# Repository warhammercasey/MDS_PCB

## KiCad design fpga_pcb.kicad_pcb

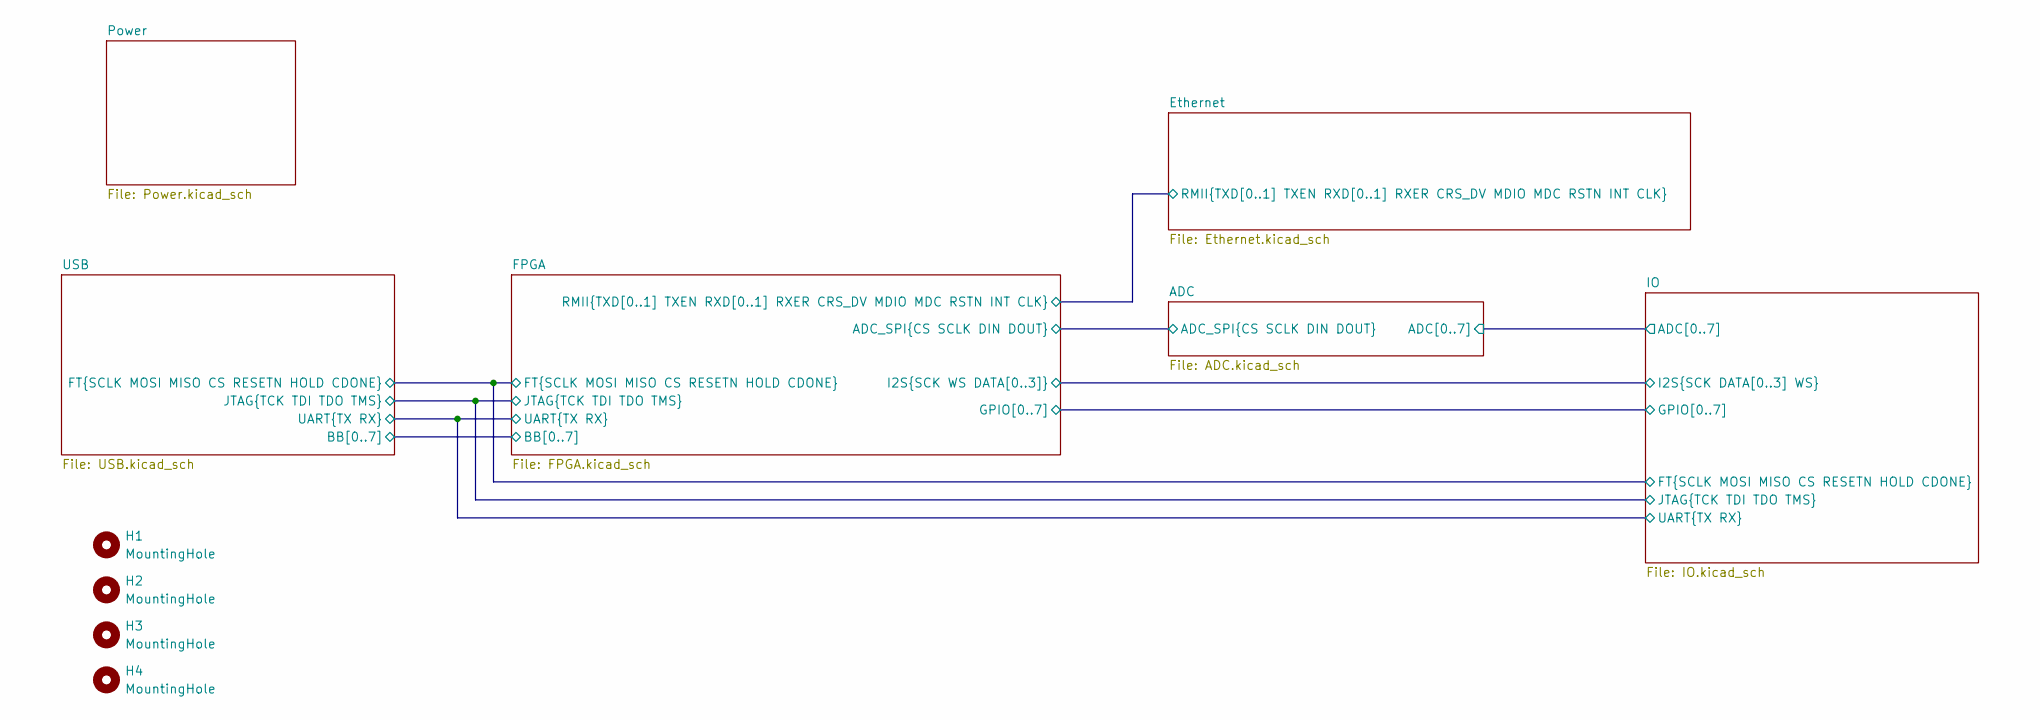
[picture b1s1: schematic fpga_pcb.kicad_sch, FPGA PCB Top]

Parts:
H1, H2, H3, H4: MountingHole; MountingHole_3.2mm_M3_DIN965_Pad

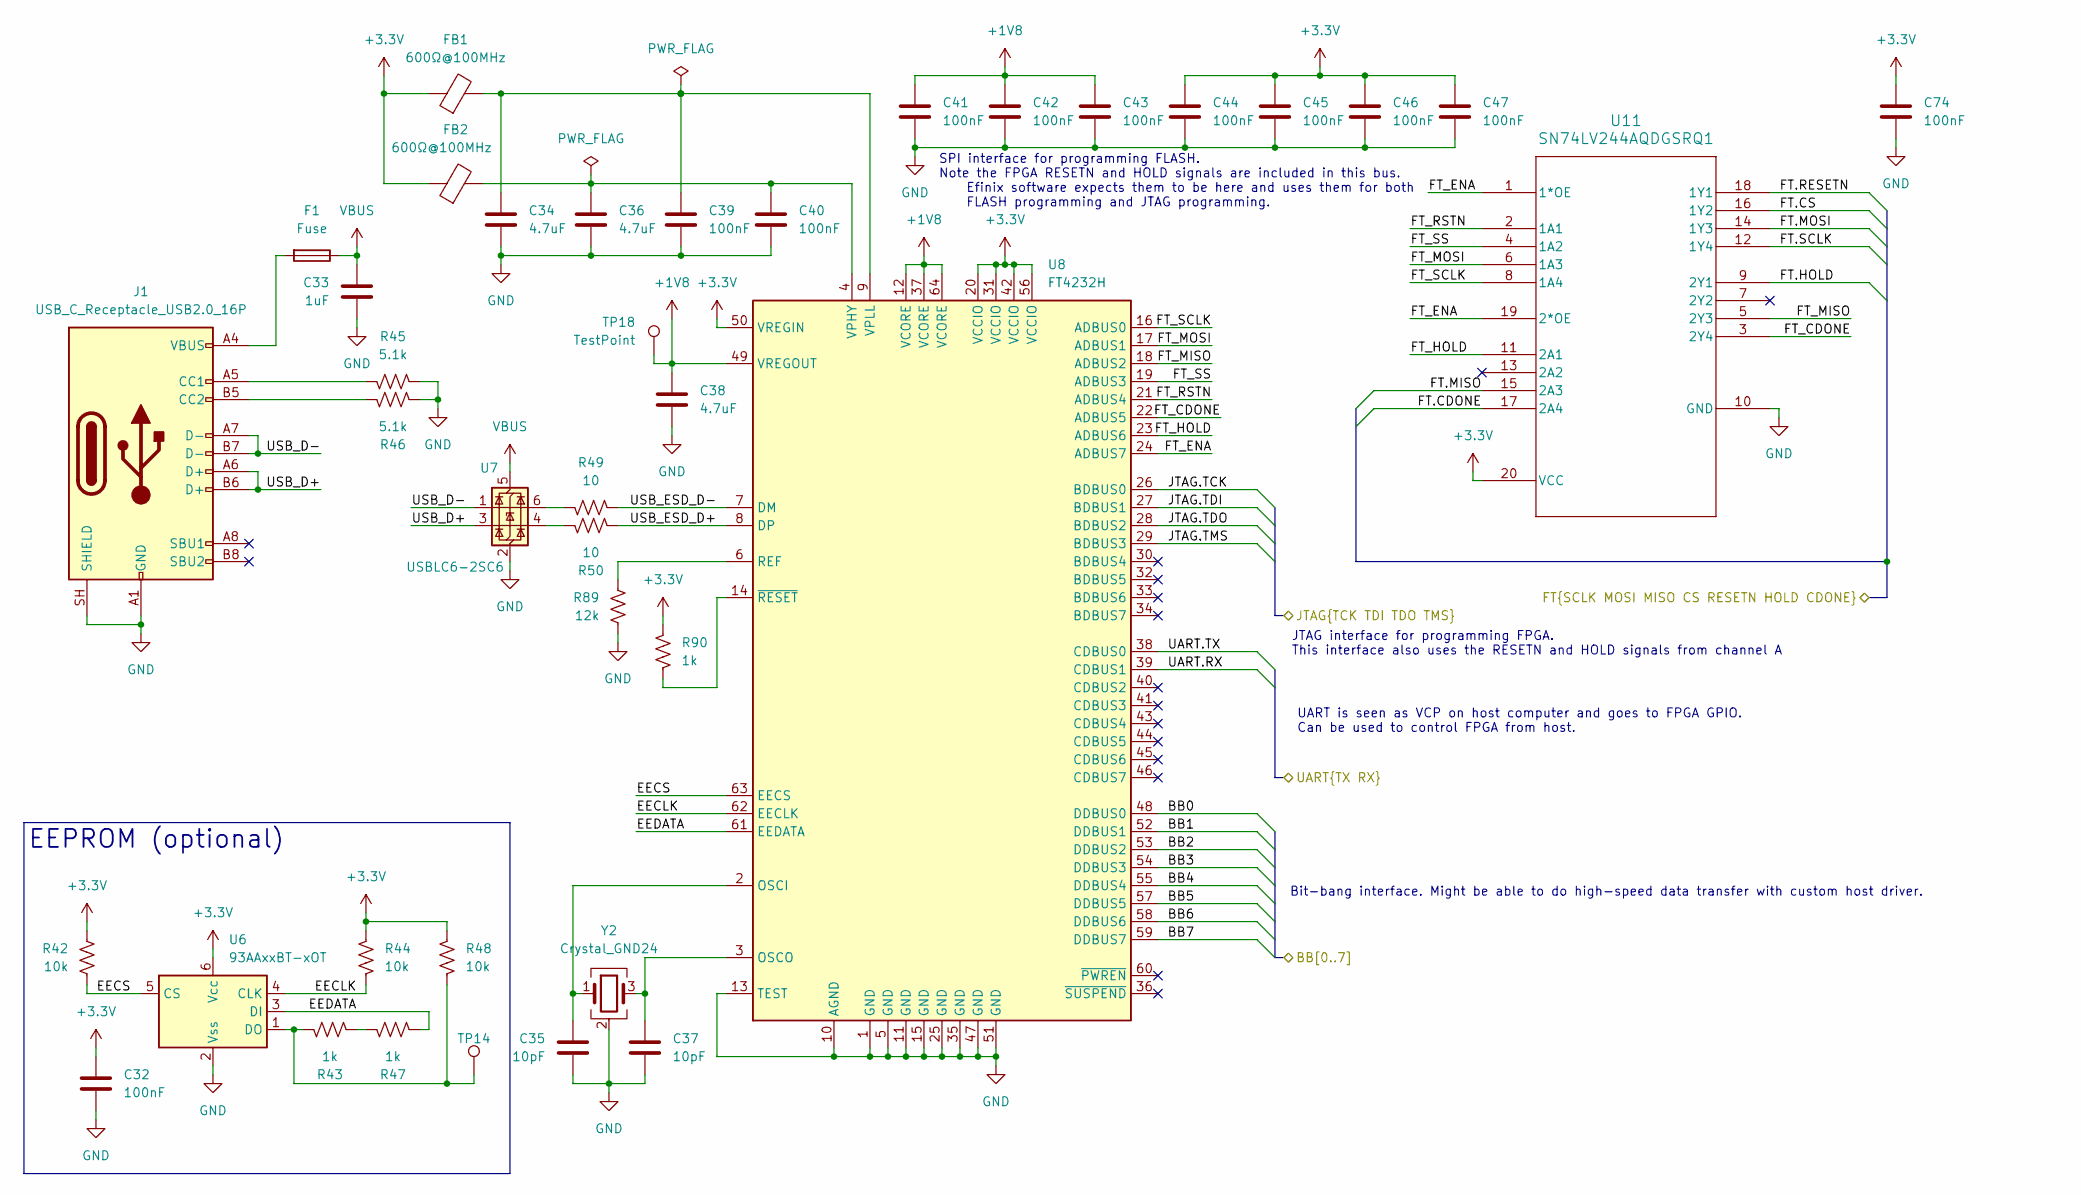
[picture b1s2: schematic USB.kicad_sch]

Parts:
C32, C39, C40, C41, C42, C43, C44, C45, C46, C47, C74: 100nF; C_0603_1608Metric; Digikey PN 1276-6854-1-ND
C33: 1uF; C_0603_1608Metric; Digikey PN 1276-1859-1-ND
C34, C36, C38: 4.7uF; C_0603_1608Metric; Digikey PN 1276-1045-1-ND
C35, C37: 10pF; C_0603_1608Metric; Digikey PN 1276-2149-1-ND
F1: Fuse; Fuse_0603_1608Metric; Digikey PN 5923-0686F7000-01CT-ND
FB1, FB2: 600Ω@100MHz; L_0603_1608Metric; Digikey PN 490-1014-1-ND
J1: USB_C_Receptacle_USB2.0_16P; USB_C_Receptacle_GCT_USB4105-xx-A_16P_TopMnt_Horizontal; Digikey PN 2073-USB4105-GF-ACT-ND
R42, R44, R48: 10k; R_0603_1608Metric; Digikey PN 311-10KLDCT-ND
R43, R47, R90: 1k; R_0603_1608Metric; Digikey PN 311-1.00KHRCT-ND
R45, R46: 5.1k; R_0603_1608Metric; Digikey PN 311-5.1KGRCT-ND
R49, R50: 10; R_0603_1608Metric; Digikey PN 311-10LDCT-ND
R89: 12k; R_0603_1608Metric; Digikey PN 311-12.0KHRCT-ND
TP14, TP18: TestPoint; TestPoint_Pad_D1.0mm
U6: 93AAxxBT-xOT; SOT-23-6; Digikey PN 93AA56BT-I/OTCT-ND
U7: USBLC6-2SC6; SOT-23-6; Mfr # USBLC6-2SC6; Digikey PN 497-5235-1-ND
U8: FT4232H; LQFP-64_10x10mm_P0.5mm
U11: SN74LV244AQDGSRQ1; VSSOP20_DGS_TEX; Digikey PN 296-SN74LV244AQDGSRQ1CT-ND
Y2: Crystal_GND24; Crystal_SMD_3225-4Pin_3.2x2.5mm; Digikey PN 2151-RH100-12.000-10-3030-TRCT-ND

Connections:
+1V8: C38.1, C41.1, C42.1, C43.1, TP18.1 (1_1), U8.12 (VCORE), U8.37 (VCORE), U8.49 (VREGOUT), U8.64 (VCORE)
+3.3V: C32.1, C44.1, C45.1, C46.1, C47.1, C74.1, FB1.1, FB2.1, R42.1, R44.1, R48.1, R90.1, U6.6 (Vcc), U8.20 (VCCIO), U8.31 (VCCIO), U8.42 (VCCIO), U8.50 (VREGIN), U8.56 (VCCIO), U11.20 (VCC); also elsewhere on the board
/FPGA/BB0: U8.48 (DDBUS0); also elsewhere on the board
/FPGA/BB1: U8.52 (DDBUS1); also elsewhere on the board
/FPGA/BB2: U8.53 (DDBUS2); also elsewhere on the board
/FPGA/BB3: U8.54 (DDBUS3); also elsewhere on the board
/FPGA/BB4: U8.55 (DDBUS4); also elsewhere on the board
/FPGA/BB5: U8.57 (DDBUS5); also elsewhere on the board
/FPGA/BB6: U8.58 (DDBUS6); also elsewhere on the board
/FPGA/BB7: U8.59 (DDBUS7); also elsewhere on the board
/FPGA/FT.CDONE: U11.17 (2A4); also elsewhere on the board
/FPGA/FT.CS: U11.16 (1Y2); also elsewhere on the board
/FPGA/FT.HOLD: U11.9 (2Y1); also elsewhere on the board
/FPGA/FT.MISO: U11.15 (2A3); also elsewhere on the board
/FPGA/FT.MOSI: U11.14 (1Y3); also elsewhere on the board
/FPGA/FT.RESETN: U11.18 (1Y1); also elsewhere on the board
/FPGA/FT.SCLK: U11.12 (1Y4); also elsewhere on the board
/FPGA/JTAG.TCK: U8.26 (BDBUS0); also elsewhere on the board
/FPGA/JTAG.TDI: U8.27 (BDBUS1); also elsewhere on the board
/FPGA/JTAG.TDO: U8.28 (BDBUS2); also elsewhere on the board
/FPGA/JTAG.TMS: U8.29 (BDBUS3); also elsewhere on the board
/FPGA/UART.RX: U8.39 (CDBUS1); also elsewhere on the board
/FPGA/UART.TX: U8.38 (CDBUS0); also elsewhere on the board
/USB/EECLK: R44.2, U6.4 (CLK), U8.62 (EECLK)
/USB/EECS: R42.2, U6.5 (CS), U8.63 (EECS)
/USB/EEDATA: R47.2, U6.3 (DI), U8.61 (EEDATA)
/USB/FT_CDONE: U8.22 (ADBUS5), U11.3 (2Y4)
/USB/FT_ENA: U8.24 (ADBUS7), U11.1 (1*OE), U11.19 (2*OE)
/USB/FT_HOLD: U8.23 (ADBUS6), U11.11 (2A1)
/USB/FT_MISO: U8.18 (ADBUS2), U11.5 (2Y3)
/USB/FT_MOSI: U8.17 (ADBUS1), U11.6 (1A3)
/USB/FT_RSTN: U8.21 (ADBUS4), U11.2 (1A1)
/USB/FT_SCLK: U8.16 (ADBUS0), U11.8 (1A4)
/USB/FT_SS: U8.19 (ADBUS3), U11.4 (1A2)
/USB/USB_D+: J1.A6 (D+), J1.B6 (D+), U7.3 (I/O2)
/USB/USB_D-: J1.A7 (D-), J1.B7 (D-), U7.1 (I/O1)
/USB/USB_ESD_D+: R50.1, U8.8 (DP)
/USB/USB_ESD_D-: R49.1, U8.7 (DM)
GND: C32.2, C33.2, C34.2, C35.2, C36.2, C37.2, C38.2, C39.2, C40.2, C41.2, C42.2, C43.2, C44.2, C45.2, C46.2, C47.2, C74.2, J1.A1 (GND), J1.A12 (GND), J1.B1 (GND), J1.B12 (GND), J1.SH (SHIELD), R45.1, R46.2, R89.2, U6.2 (Vss), U7.2 (GND), U8.1 (GND), U8.5 (GND), U8.10 (AGND), U8.11 (GND), U8.13 (TEST), U8.15 (GND), U8.25 (GND), U8.35 (GND), U8.47 (GND), U8.51 (GND), U11.10 (GND), Y2.2 (G), Y2.4 (G); also elsewhere on the board
unnamed: F1.2, J1.A4 (VBUS), J1.A9 (VBUS), J1.B4 (VBUS), J1.B9 (VBUS)
unnamed: J1.A5 (CC1), R45.2
unnamed: J1.B5 (CC2), R46.1
unnamed: R43.1, R47.1
unnamed: R49.2, U7.6 (I/O1)
unnamed: R50.2, U7.4 (I/O2)
unnamed: R43.2, R48.2, TP14.1 (1_1), U6.1 (DO)
unnamed: C35.1, U8.2 (OSCI), Y2.1
unnamed: C37.1, U8.3 (OSCO), Y2.3
unnamed: R89.1, U8.6 (REF)
unnamed: C36.1, C40.1, FB2.2, U8.4 (VPHY)
unnamed: C34.1, C39.1, FB1.2, U8.9 (VPLL)
unnamed: R90.2, U8.14 (~RESET)
VBUS: C33.1, F1.1, U7.5 (VBUS); also elsewhere on the board

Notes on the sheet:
EEPROM (optional)
SPI interface for programming FLASH. Note the FPGA RESETN and HOLD signals are included in this bus. Efinix software expects them to be here and uses them for both FLASH programming and JTAG programming.
UART is seen as VCP on host computer and goes to FPGA GPIO. Can be used to control FPGA from host.
JTAG interface for programming FPGA. This interface also uses the RESETN and HOLD signals from channel A
Bit-bang interface. Might be able to do high-speed data transfer with custom host driver.

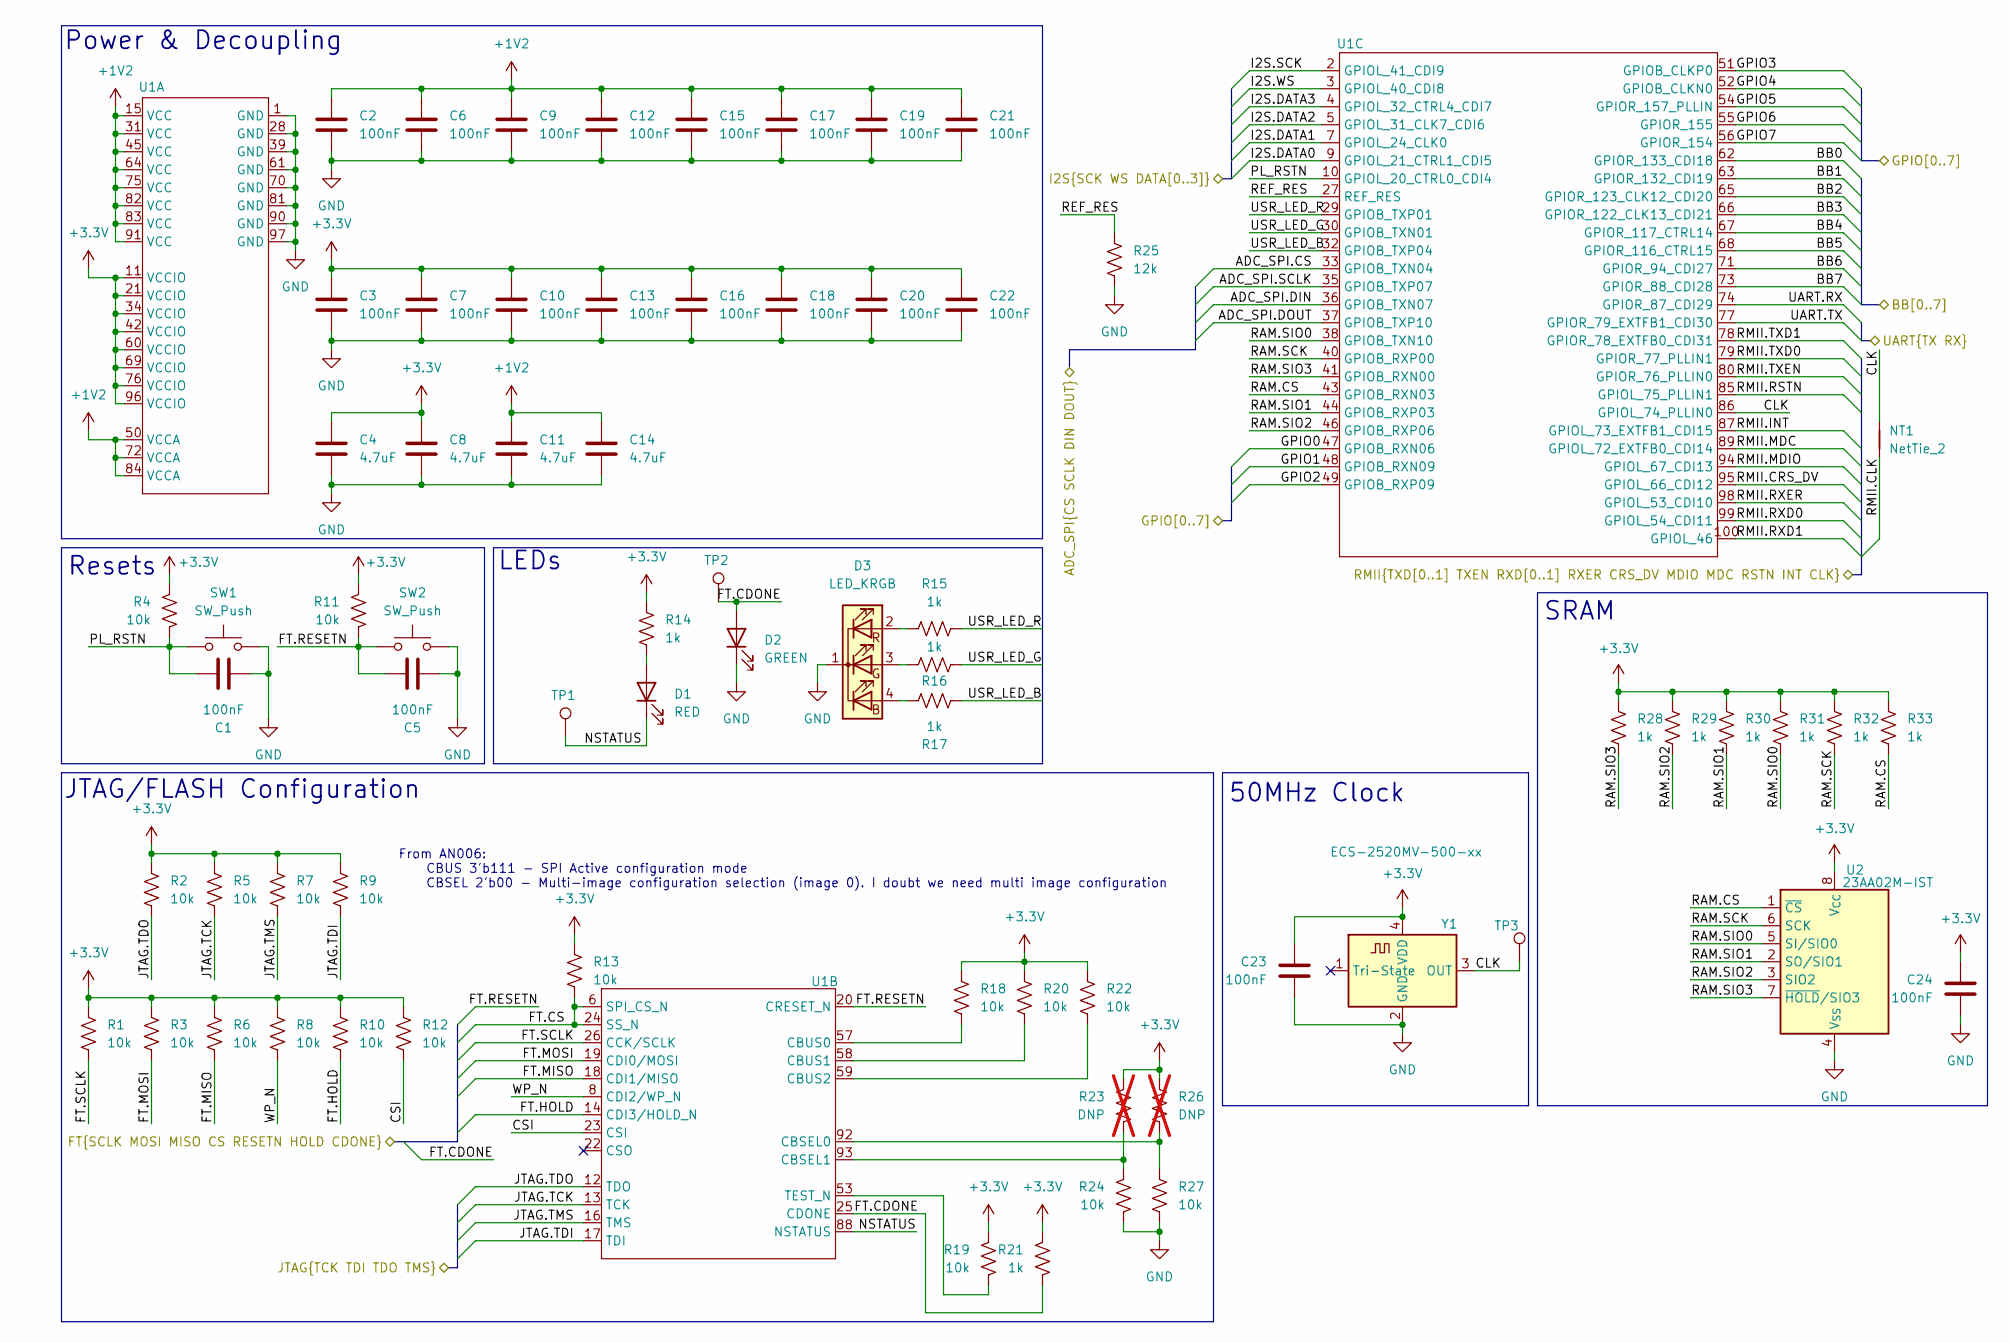
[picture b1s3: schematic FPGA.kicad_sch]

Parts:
C1, C2, C3, C5, C6, C7, C9, C10, C12, C13, C15, C16, C17, C18, C19, C20, C21, C22, C23, C24: 100nF; C_0603_1608Metric; Digikey PN 1276-6854-1-ND
C4, C8, C11, C14: 4.7uF; C_0603_1608Metric; Digikey PN 1276-1045-1-ND
D1: RED; LED_0603_1608Metric; Digikey PN 754-1123-1-ND
D2: GREEN; LED_0603_1608Metric; Digikey PN 754-1121-1-ND
D3: LED_KRGB; LED_LiteOn_LTST-C19HE1WT; Digikey PN 160-2162-1-ND
NT1: NetTie_2; NetTie-2_SMD_Pad0.5mm
R1, R2, R3, R4, R5, R6, R7, R8, R9, R10, R11, R12, R13, R18, R19, R20, R22, R24, R27: 10k; R_0603_1608Metric; Digikey PN 311-10KLDCT-ND
R14, R15, R16, R17, R21, R28, R29, R30, R31, R32, R33: 1k; R_0603_1608Metric; Digikey PN 311-1.00KHRCT-ND
R23, R26: DNP; R_0603_1608Metric; not fitted
R25: 12k; R_0603_1608Metric; Digikey PN 311-12.0KHRCT-ND
SW1, SW2: SW_Push; SW_Push_1P1T_NO_CK_KMR2; Digikey PN CKN10244CT-ND
TP1, TP2, TP3: TestPoint; TestPoint_Pad_D1.0mm
U1: LQFP-100_14x14mm_P0.5mm; DigiKey PN 2134-T20Q100F3C3-ND
U2: 23AA02M-IST; TSSOP-8_4.4x3mm_P0.65mm; Digikey PN 150-23AA02M-I/ST-ND
Y1: ECS-2520MV-500-xx; Oscillator_SMD_ECS_2520MV-xxx-xx-4Pin_2.5x2.0mm; Digikey PN XC2758CT-ND

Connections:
+1V2: C2.1, C6.1, C9.1, C11.1, C12.1, C14.1, C15.1, C17.1, C19.1, C21.1, U1.15 (VCC), U1.31 (VCC), U1.45 (VCC), U1.50 (VCCA), U1.64 (VCC), U1.72 (VCCA), U1.75 (VCC), U1.82 (VCC), U1.83 (VCC), U1.84 (VCCA), U1.91 (VCC); also elsewhere on the board
+3.3V: C3.1, C4.1, C7.1, C8.1, C10.1, C13.1, C16.1, C18.1, C20.1, C22.1, C23.1, C24.1, R1.1, R2.1, R3.1, R4.1, R5.1, R6.1, R7.1, R8.1, R9.1, R10.1, R11.1, R12.1, R13.1, R14.1, R18.1, R19.1, R20.1, R21.1, R22.1, R23.1, R26.1, R28.1, R29.1, R30.1, R31.1, R32.1, R33.1, U1.11 (VCCIO), U1.21 (VCCIO), U1.34 (VCCIO), U1.42 (VCCIO), U1.60 (VCCIO), U1.69 (VCCIO), U1.76 (VCCIO), U1.96 (VCCIO), U2.8 (V_{CC}), Y1.4 (VDD); also elsewhere on the board
/ADC/ADC_SPI.CS: U1.33 (GPIOB_TXN04); also elsewhere on the board
/ADC/ADC_SPI.DIN: U1.36 (GPIOB_TXN07); also elsewhere on the board
/ADC/ADC_SPI.DOUT: U1.37 (GPIOB_TXP10); also elsewhere on the board
/ADC/ADC_SPI.SCLK: U1.35 (GPIOB_TXP07); also elsewhere on the board
/Ethernet/RMII.CLK: NT1.1; also elsewhere on the board
/Ethernet/RMII.CRS_DV: U1.95 (GPIOL_66_CDI12); also elsewhere on the board
/Ethernet/RMII.INT: U1.87 (GPIOL_73_EXTFB1_CDI15); also elsewhere on the board
/Ethernet/RMII.MDC: U1.89 (GPIOL_72_EXTFB0_CDI14); also elsewhere on the board
/Ethernet/RMII.MDIO: U1.94 (GPIOL_67_CDI13); also elsewhere on the board
/Ethernet/RMII.RSTN: U1.85 (GPIOL_75_PLLIN1); also elsewhere on the board
/Ethernet/RMII.RXD0: U1.99 (GPIOL_54_CDI11); also elsewhere on the board
/Ethernet/RMII.RXD1: U1.100 (GPIOL_46); also elsewhere on the board
/Ethernet/RMII.RXER: U1.98 (GPIOL_53_CDI10); also elsewhere on the board
/Ethernet/RMII.TXD0: U1.79 (GPIOR_77_PLLIN1); also elsewhere on the board
/Ethernet/RMII.TXD1: U1.78 (GPIOR_78_EXTFB0_CDI31); also elsewhere on the board
/Ethernet/RMII.TXEN: U1.80 (GPIOR_76_PLLIN0); also elsewhere on the board
/FPGA/BB0: U1.62 (GPIOR_133_CDI18); also elsewhere on the board
/FPGA/BB1: U1.63 (GPIOR_132_CDI19); also elsewhere on the board
/FPGA/BB2: U1.65 (GPIOR_123_CLK12_CDI20); also elsewhere on the board
/FPGA/BB3: U1.66 (GPIOR_122_CLK13_CDI21); also elsewhere on the board
/FPGA/BB4: U1.67 (GPIOR_117_CTRL14); also elsewhere on the board
/FPGA/BB5: U1.68 (GPIOR_116_CTRL15); also elsewhere on the board
/FPGA/BB6: U1.71 (GPIOR_94_CDI27); also elsewhere on the board
/FPGA/BB7: U1.73 (GPIOR_88_CDI28); also elsewhere on the board
/FPGA/CLK: NT1.2, TP3.1 (1_1), U1.86 (GPIOL_74_PLLIN0), Y1.3 (OUT)
/FPGA/CSI: R12.2, U1.23 (CSI)
/FPGA/FT.CDONE: D2.2 (A), R21.2, TP2.1 (1_1), U1.25 (CDONE); also elsewhere on the board
/FPGA/FT.CS: R13.2, U1.6 (SPI_CS_N), U1.24 (SS_N); also elsewhere on the board
/FPGA/FT.HOLD: R10.2, U1.14 (CDI3/HOLD_N); also elsewhere on the board
/FPGA/FT.MISO: R6.2, U1.18 (CDI1/MISO); also elsewhere on the board
/FPGA/FT.MOSI: R3.2, U1.19 (CDI0/MOSI); also elsewhere on the board
/FPGA/FT.RESETN: C5.2, R11.2, SW2.1, U1.20 (CRESET_N); also elsewhere on the board
/FPGA/FT.SCLK: R1.2, U1.26 (CCK/SCLK); also elsewhere on the board
/FPGA/GPIO0: U1.47 (GPIOB_RXN06); also elsewhere on the board
/FPGA/GPIO1: U1.48 (GPIOB_RXN09); also elsewhere on the board
/FPGA/GPIO2: U1.49 (GPIOB_RXP09); also elsewhere on the board
/FPGA/GPIO3: U1.51 (GPIOB_CLKP0); also elsewhere on the board
/FPGA/GPIO4: U1.52 (GPIOB_CLKN0); also elsewhere on the board
/FPGA/GPIO5: U1.54 (GPIOR_157_PLLIN); also elsewhere on the board
/FPGA/GPIO6: U1.55 (GPIOR_155); also elsewhere on the board
/FPGA/GPIO7: U1.56 (GPIOR_154); also elsewhere on the board
/FPGA/I2S.DATA0: U1.9 (GPIOL_21_CTRL1_CDI5); also elsewhere on the board
/FPGA/I2S.DATA1: U1.7 (GPIOL_24_CLK0); also elsewhere on the board
/FPGA/I2S.DATA2: U1.5 (GPIOL_31_CLK7_CDI6); also elsewhere on the board
/FPGA/I2S.DATA3: U1.4 (GPIOL_32_CTRL4_CDI7); also elsewhere on the board
/FPGA/I2S.SCK: U1.2 (GPIOL_41_CDI9); also elsewhere on the board
/FPGA/I2S.WS: U1.3 (GPIOL_40_CDI8); also elsewhere on the board
/FPGA/JTAG.TCK: R5.2, U1.13 (TCK); also elsewhere on the board
/FPGA/JTAG.TDI: R9.2, U1.17 (TDI); also elsewhere on the board
/FPGA/JTAG.TDO: R2.2, U1.12 (TDO); also elsewhere on the board
/FPGA/JTAG.TMS: R7.2, U1.16 (TMS); also elsewhere on the board
/FPGA/NSTATUS: D1.1 (K), TP1.1 (1_1), U1.88 (NSTATUS)
/FPGA/PL_RSTN: C1.2, R4.2, SW1.1, U1.10 (GPIOL_20_CTRL0_CDI4)
/FPGA/RAM.CS: R33.2, U1.43 (GPIOB_RXN03), U2.1 (~CS)
/FPGA/RAM.SCK: R32.2, U1.40 (GPIOB_RXP00), U2.6 (SCK)
/FPGA/RAM.SIO0: R31.2, U1.38 (GPIOB_TXN10), U2.5 (SI/SIO0)
/FPGA/RAM.SIO1: R30.2, U1.44 (GPIOB_RXP03), U2.2 (SO/SIO1)
/FPGA/RAM.SIO2: R29.2, U1.46 (GPIOB_RXP06), U2.3 (SIO2)
/FPGA/RAM.SIO3: R28.2, U1.41 (GPIOB_RXN00), U2.7 (~HOLD/SIO3)
/FPGA/REF_RES: R25.1, U1.27 (REF_RES)
/FPGA/UART.RX: U1.74 (GPIOR_87_CDI29); also elsewhere on the board
/FPGA/UART.TX: U1.77 (GPIOR_79_EXTFB1_CDI30); also elsewhere on the board
/FPGA/USR_LED_B: R17.1, U1.32 (GPIOB_TXP04)
/FPGA/USR_LED_G: R16.2, U1.30 (GPIOB_TXN01)
/FPGA/USR_LED_R: R15.2, U1.29 (GPIOB_TXP01)
/FPGA/WP_N: R8.2, U1.8 (CDI2/WP_N)
GND: C1.1, C2.2, C3.2, C4.2, C5.1, C6.2, C7.2, C8.2, C9.2, C10.2, C11.2, C12.2, C13.2, C14.2, C15.2, C16.2, C17.2, C18.2, C19.2, C20.2, C21.2, C22.2, C23.2, C24.2, D2.1 (K), D3.1 (K), R24.2, R25.2, R27.2, SW1.2, SW2.2, U1.1 (GND), U1.28 (GND), U1.39 (GND), U1.61 (GND), U1.70 (GND), U1.81 (GND), U1.90 (GND), U1.97 (GND), U2.4 (V_{SS}), Y1.2 (GND); also elsewhere on the board
unnamed: D1.2 (A), R14.2
unnamed: D3.4 (BA), R17.2
unnamed: D3.3 (GA), R16.1
unnamed: D3.2 (RA), R15.1
unnamed: R26.2, R27.1, U1.92 (CBSEL0)
unnamed: R23.2, R24.1, U1.93 (CBSEL1)
unnamed: R18.2, U1.57 (CBUS0)
unnamed: R20.2, U1.58 (CBUS1)
unnamed: R22.2, U1.59 (CBUS2)
unnamed: R19.2, U1.53 (TEST_N)

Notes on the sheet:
JTAG/FLASH Configuration
LEDs
SRAM
Power & Decoupling
50MHz Clock
Resets
From AN006: CBUS 3'b111 - SPI Active configuration mode CBSEL 2'b00 - Multi-image configuration selection (image 0). I doubt we need multi image configuration

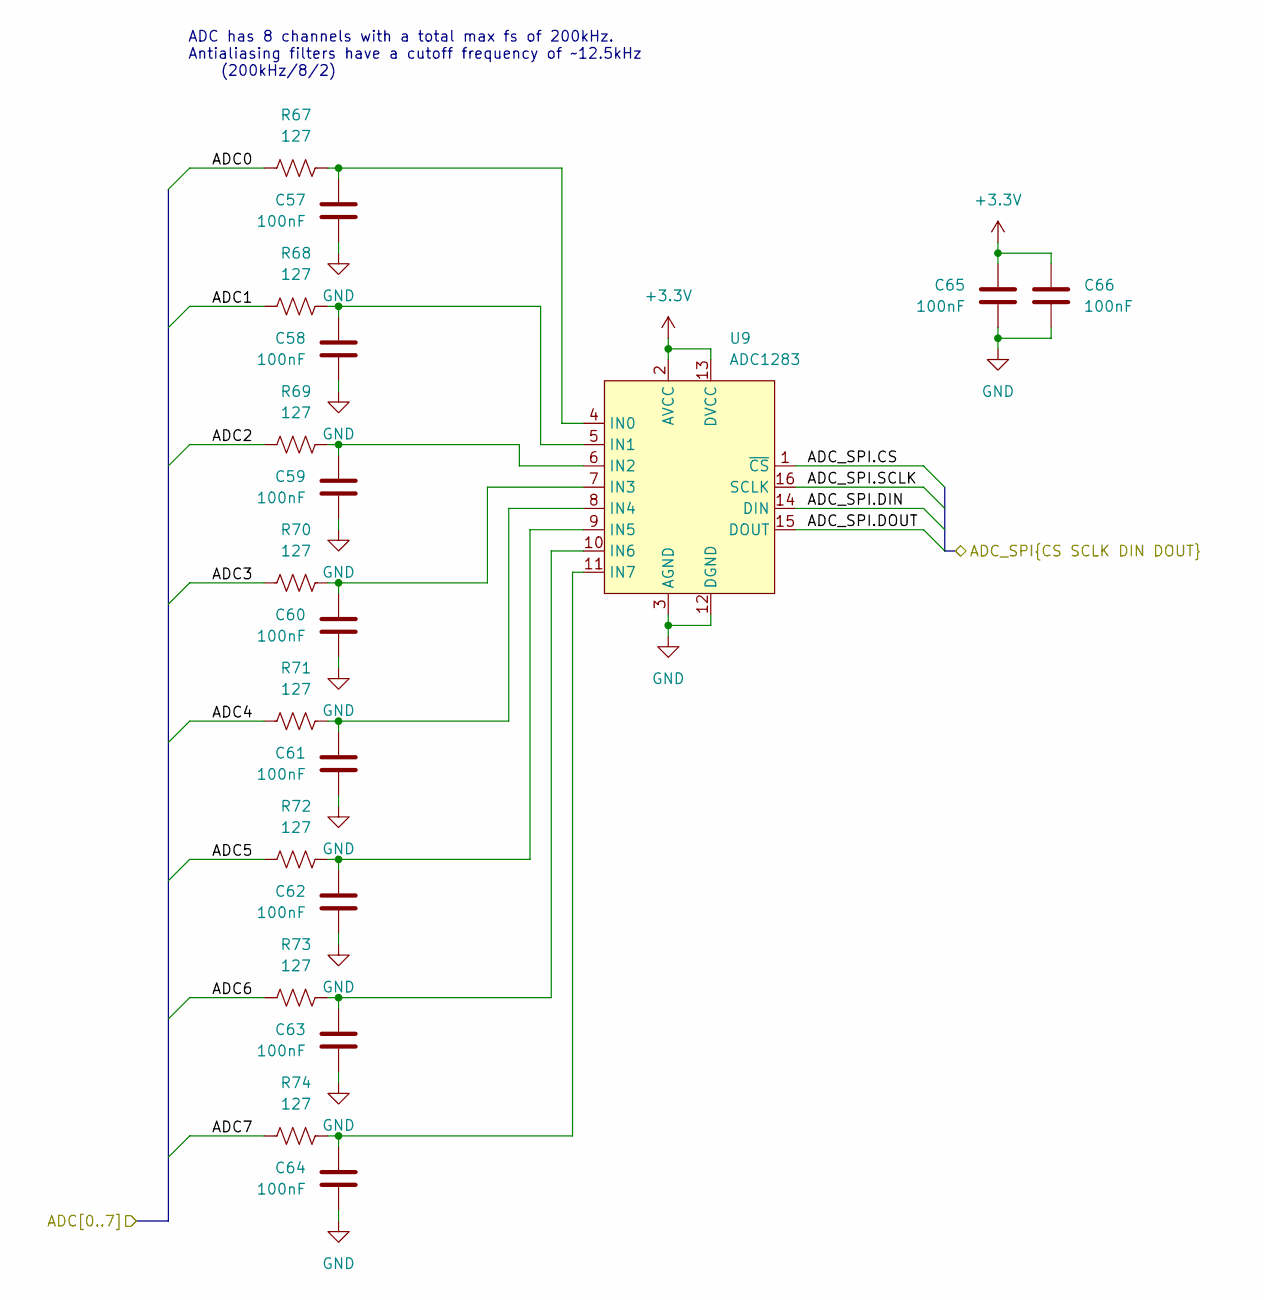
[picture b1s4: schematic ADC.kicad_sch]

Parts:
C57, C58, C59, C60, C61, C62, C63, C64, C65, C66: 100nF; C_0603_1608Metric; Digikey PN 1276-6854-1-ND
R67, R68, R69, R70, R71, R72, R73, R74: 127; R_0603_1608Metric; Digikey PN 311-127HRCT-ND
U9: ADC1283; TSSOP-16_4.4x5mm_P0.65mm; Digikey PN ADC088S022CIMTX/NOPBCT-ND

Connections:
+3.3V: C65.1, C66.1, U9.2 (AVCC), U9.13 (DVCC); also elsewhere on the board
/ADC/ADC0: R67.1; also elsewhere on the board
/ADC/ADC1: R68.1; also elsewhere on the board
/ADC/ADC2: R69.1; also elsewhere on the board
/ADC/ADC3: R70.1; also elsewhere on the board
/ADC/ADC4: R71.1; also elsewhere on the board
/ADC/ADC5: R72.1; also elsewhere on the board
/ADC/ADC6: R73.1; also elsewhere on the board
/ADC/ADC7: R74.1; also elsewhere on the board
/ADC/ADC_SPI.CS: U9.1 (~CS); also elsewhere on the board
/ADC/ADC_SPI.DIN: U9.14 (DIN); also elsewhere on the board
/ADC/ADC_SPI.DOUT: U9.15 (DOUT); also elsewhere on the board
/ADC/ADC_SPI.SCLK: U9.16 (SCLK); also elsewhere on the board
GND: C57.2, C58.2, C59.2, C60.2, C61.2, C62.2, C63.2, C64.2, C65.2, C66.2, U9.3 (AGND), U9.12 (DGND); also elsewhere on the board
unnamed: C57.1, R67.2, U9.4 (IN0)
unnamed: C58.1, R68.2, U9.5 (IN1)
unnamed: C59.1, R69.2, U9.6 (IN2)
unnamed: C60.1, R70.2, U9.7 (IN3)
unnamed: C61.1, R71.2, U9.8 (IN4)
unnamed: C62.1, R72.2, U9.9 (IN5)
unnamed: C63.1, R73.2, U9.10 (IN6)
unnamed: C64.1, R74.2, U9.11 (IN7)

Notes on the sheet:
ADC has 8 channels with a total max fs of 200kHz. Antialiasing filters have a cutoff frequency of ~12.5kHz (200kHz/8/2)

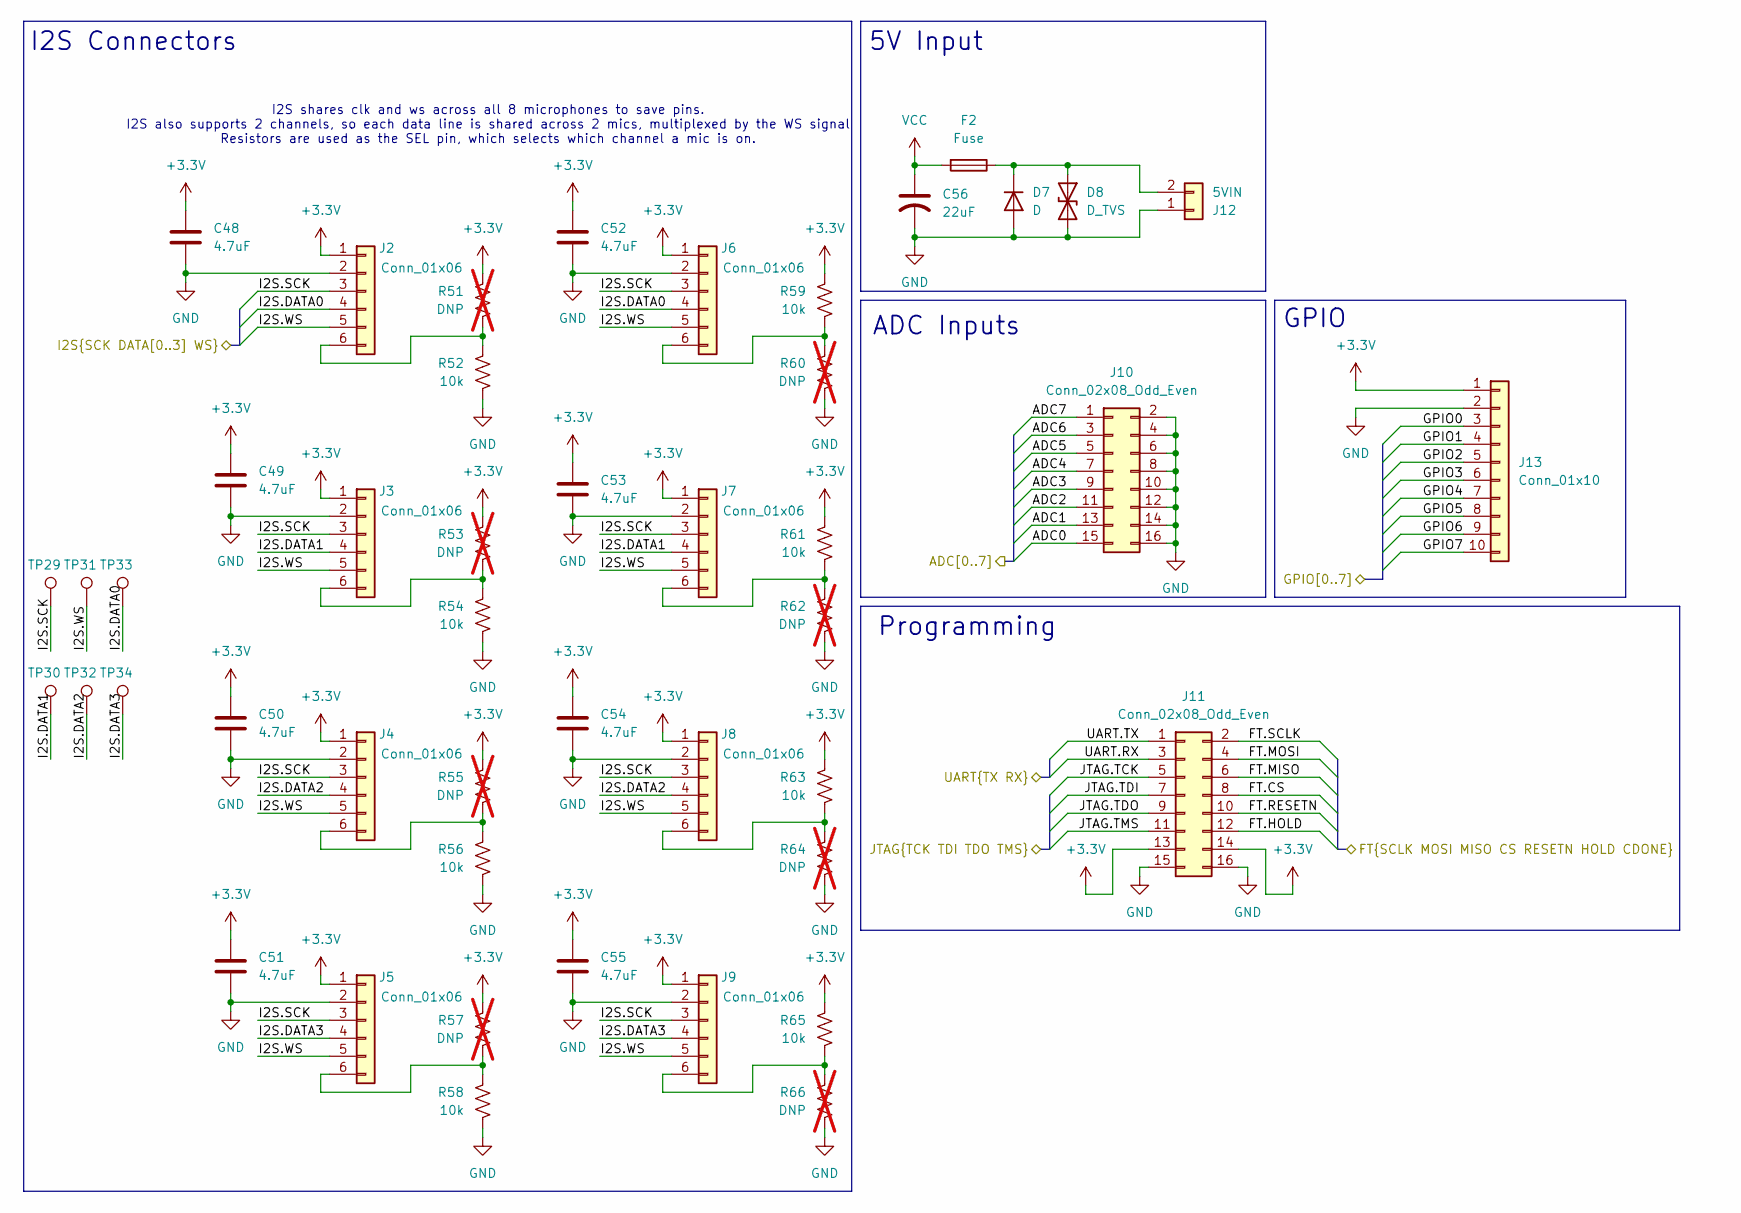
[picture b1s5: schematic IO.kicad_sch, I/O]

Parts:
C48, C49, C50, C51, C52, C53, C54, C55: 4.7uF; C_0603_1608Metric; Digikey PN 1276-1045-1-ND
C56: 22uF; C_Radial_D5.0mm_H7.0mm_P2.00mm; Digikey PN P814-ND
D7: D; D_SMA; Digikey PN 5399-SS32CT-ND
D8: D_TVS; D_SMA; Digikey PN 5399-SMAJ6.0ACT-ND
F2: Fuse; Fuse_0603_1608Metric; Digikey PN 5923-0686F7000-01CT-ND
J2, J3, J4, J5, J6, J7, J8, J9: Conn_01x06; JST_GH_BM06B-GHS-TBT_1x06-1MP_P1.25mm_Vertical; Digikey PN 455-BM06B-GHS-TBTCT-ND
J10, J11: Conn_02x08_Odd_Even; PinHeader_2x08_P2.54mm_Vertical; Digikey PN 4627-PH254V-216-6TBKG126-ND
J12: 5VIN; JST_XH_B2B-XH-A_1x02_P2.50mm_Vertical; Digikey PN 455-B2B-XH-A-ND
J13: Conn_01x10; PinHeader_1x10_P2.54mm_Vertical; Digikey PN 2057-PH1-10-UA-ND
R51, R53, R55, R57, R60, R62, R64, R66: DNP; R_0603_1608Metric; not fitted
R52, R54, R56, R58, R59, R61, R63, R65: 10k; R_0603_1608Metric; Digikey PN 311-10KLDCT-ND
TP29, TP30, TP31, TP32, TP33, TP34: TestPoint; TestPoint_Pad_D1.0mm

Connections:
+3.3V: C48.1, C49.1, C50.1, C51.1, C52.1, C53.1, C54.1, C55.1, J2.1, J3.1, J4.1, J5.1, J6.1, J7.1, J8.1, J9.1, J11.13, J11.14, J13.1, R51.1, R53.1, R55.1, R57.1, R59.1, R61.1, R63.1, R65.1; also elsewhere on the board
/ADC/ADC0: J10.15; also elsewhere on the board
/ADC/ADC1: J10.13; also elsewhere on the board
/ADC/ADC2: J10.11; also elsewhere on the board
/ADC/ADC3: J10.9; also elsewhere on the board
/ADC/ADC4: J10.7; also elsewhere on the board
/ADC/ADC5: J10.5; also elsewhere on the board
/ADC/ADC6: J10.3; also elsewhere on the board
/ADC/ADC7: J10.1; also elsewhere on the board
/FPGA/FT.CS: J11.8; also elsewhere on the board
/FPGA/FT.HOLD: J11.12; also elsewhere on the board
/FPGA/FT.MISO: J11.6; also elsewhere on the board
/FPGA/FT.MOSI: J11.4; also elsewhere on the board
/FPGA/FT.RESETN: J11.10; also elsewhere on the board
/FPGA/FT.SCLK: J11.2; also elsewhere on the board
/FPGA/GPIO0: J13.3; also elsewhere on the board
/FPGA/GPIO1: J13.4; also elsewhere on the board
/FPGA/GPIO2: J13.5; also elsewhere on the board
/FPGA/GPIO3: J13.6; also elsewhere on the board
/FPGA/GPIO4: J13.7; also elsewhere on the board
/FPGA/GPIO5: J13.8; also elsewhere on the board
/FPGA/GPIO6: J13.9; also elsewhere on the board
/FPGA/GPIO7: J13.10; also elsewhere on the board
/FPGA/I2S.DATA0: J2.4, J6.4, TP33.1 (1_1); also elsewhere on the board
/FPGA/I2S.DATA1: J3.4, J7.4, TP30.1 (1_1); also elsewhere on the board
/FPGA/I2S.DATA2: J4.4, J8.4, TP32.1 (1_1); also elsewhere on the board
/FPGA/I2S.DATA3: J5.4, J9.4, TP34.1 (1_1); also elsewhere on the board
/FPGA/I2S.SCK: J2.3, J3.3, J4.3, J5.3, J6.3, J7.3, J8.3, J9.3, TP29.1 (1_1); also elsewhere on the board
/FPGA/I2S.WS: J2.5, J3.5, J4.5, J5.5, J6.5, J7.5, J8.5, J9.5, TP31.1 (1_1); also elsewhere on the board
/FPGA/JTAG.TCK: J11.5; also elsewhere on the board
/FPGA/JTAG.TDI: J11.7; also elsewhere on the board
/FPGA/JTAG.TDO: J11.9; also elsewhere on the board
/FPGA/JTAG.TMS: J11.11; also elsewhere on the board
/FPGA/UART.RX: J11.3; also elsewhere on the board
/FPGA/UART.TX: J11.1; also elsewhere on the board
GND: C48.2, C49.2, C50.2, C51.2, C52.2, C53.2, C54.2, C55.2, C56.2, D7.2 (A), D8.2 (A2), J2.2, J3.2, J4.2, J5.2, J6.2, J7.2, J8.2, J9.2, J10.2, J10.4, J10.6, J10.8, J10.10, J10.12, J10.14, J10.16, J11.15, J11.16, J12.1, J13.2, R52.2, R54.2, R56.2, R58.2, R60.2, R62.2, R64.2, R66.2; also elsewhere on the board
unnamed: D7.1 (K), D8.1 (A1), F2.1, J12.2
unnamed: J2.6, R51.2, R52.1
unnamed: J3.6, R53.2, R54.1
unnamed: J4.6, R55.2, R56.1
unnamed: J5.6, R57.2, R58.1
unnamed: J6.6, R59.2, R60.1
unnamed: J7.6, R61.2, R62.1
unnamed: J8.6, R63.2, R64.1
unnamed: J9.6, R65.2, R66.1
VCC: C56.1, F2.2; also elsewhere on the board

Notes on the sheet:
I2S Connectors
ADC Inputs
I2S shares clk and ws across all 8 microphones to save pins. I2S also supports 2 channels, so each data line is shared across 2 mics, multiplexed by the WS signal Resistors are used as the SEL pin, which selects which channel a mic is on.
Programming
GPIO
5V Input
